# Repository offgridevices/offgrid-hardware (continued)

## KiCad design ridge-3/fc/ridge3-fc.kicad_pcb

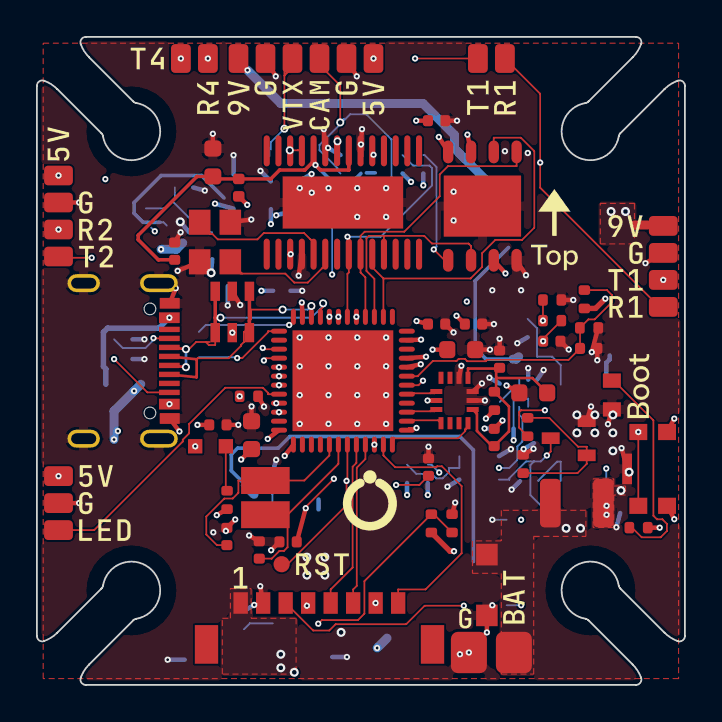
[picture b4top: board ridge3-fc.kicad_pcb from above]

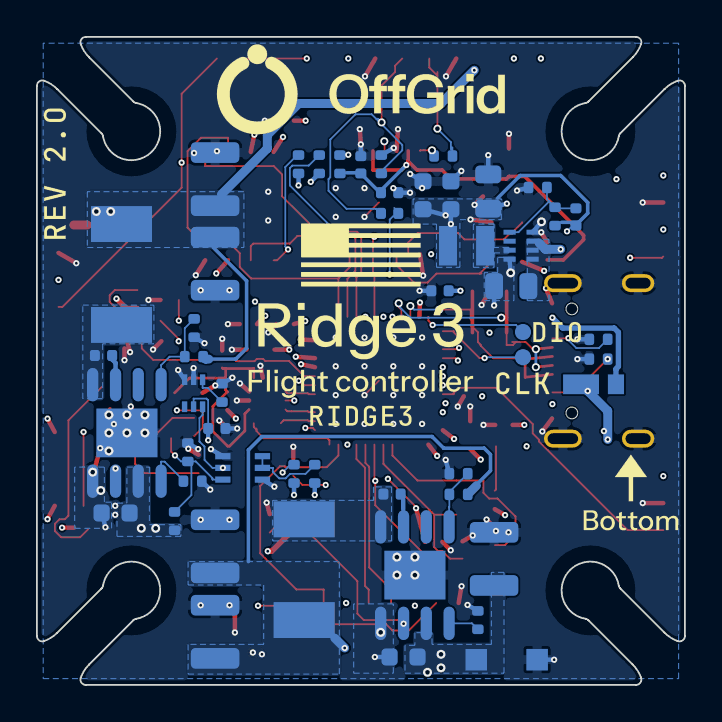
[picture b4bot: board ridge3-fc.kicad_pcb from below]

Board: 6 copper layers, 36.0 x 36.0 mm, 124 parts (51 on the bottom side), 70 nets.

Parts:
C1, C2, C5, C10, C11, C19, C20, C21, C22, C23, C26, C30, C31, C32, C34, C35, C36, C37: 100nF; C_0402_1005Metric
C3, C8: 10uF; C_1210_3225Metric
C4, C9: 100nF; C_0603_1608Metric
C6, C7, C12, C13: 22uF; C_1210_3225Metric
C14, C17: 10uF; C_0805_2012Metric
C15, C16, C25, C29, C33: 4.7uF; C_0603_1608Metric
C18, C27, C28: 10pF; C_0402_1005Metric
C24: 1uF; C_0603_1608Metric
D_TVS, D_TVS9: SMF33A; SMF_L2.8-W1.8-LS3.7-RD
D_USB: RB160VAM-40; SOD-323HE_L2.0-W1.4-LS2.5-RD
FB_OSD: 600R@100MHz; L_0402_1005Metric
H1, H2, H3, H4: HOLE; MOUNT_M2_SLOT
J_ESC: Micro-Lock Plus 8P RA; CONN-SMD_8P-P1.25_5055670871
J_USB: USB-C; USB-C-SMD_MC-311D
LED_PWR: RED; LED0603-RD_1
LED_STAT: BLUE; LED0603-R-RD_BLUE
L_3V3: 0.47uH; IND-SMD_L2.5-W2.0_TFM252012ALMA2R2MTAA
L_5V, L_9V: 15uH; IND-SMD_L7.1-W6.5_SPM6530T
P_5V: PAD_SIG
P_BAT: PAD_MOTOR
P_BATG: PAD_MOTOR
P_CAM, P_CAM5V: PAD_SIG
P_CAMG: PAD_SIG
P_G1: PAD_SIG
P_HD9V: PAD_SIG
P_HDG: PAD_SIG
P_HDR: PAD_SIG
P_HDT: PAD_SIG
P_LED: PAD_SIG
P_R1, P_R2, P_R4: PAD_SIG
P_RX5V: PAD_SIG
P_RXG: PAD_SIG
P_T1, P_T2, P_T4: PAD_SIG
P_VTX, P_VTX9V: PAD_SIG
P_VTXG: PAD_SIG
Q_TSW: BSS138DW; SC-70-6_L2.0-W1.3-P0.65-LS2.1-BL
Q_VTX: AO3400A; SOT-23-3_L2.9-W1.3-P1.90-LS2.4-BR
R1, R6, R8, R11, R14, R17, R18, R20: 100k; R_0402_1005Metric
R2, R31: 1k; R_0402_1005Metric
R3: 30k; R_0402_1005Metric
R4: 2k; R_0402_1005Metric
R5, R10: 57.6k; R_0402_1005Metric
R7, R9, R12: 24.9k; R_0402_1005Metric
R13: 100R; R_0402_1005Metric
R15: 121k; R_0402_1005Metric
R16, R24, R25, R26: 10k; R_0402_1005Metric
R19: 12.4k; R_0402_1005Metric
R21: 22.1k; R_0402_1005Metric
R22: 3.3k; R_0402_1005Metric
R23: 10R; R_0402_1005Metric
R27, R28: 75R; R_0402_1005Metric
R29, R30: 5.1k; R_0402_1005Metric
R32: 330R; R_0402_1005Metric
SW_BOOT: BOOT; SW-SMD_5P-L4.2-W2.8-P1.60-LS4.6-TR
TP_NRST: PAD_TP
TP_SWCLK: PAD_TP
TP_SWDIO: PAD_TP
U_BUCK3: TPS628501; SOT-583-8_L2.1-W1.6-P0.50-LS1.6-BL
U_BUCK5, U_BUCK9: LMR38020F; ESOP-8_L4.9-W3.9-P1.27-LS6.0-BL-EP-1
U_ESD: USBLC6-2SC6; SOT-23-6_L2.9-W1.6-P0.95-LS2.8-BL
U_FC: STM32G473CEU6; UFQFPN-48_L7.0-W7.0-P0.50-BL-EP5.6
U_FLASH: S25FL128LAGNFM010; WSON-8_L6.0-W5.0-P1.27-BL-EP
U_IMU: IIM-42652; LGA-14_L3.0-W2.5-P0.50-TL
U_OSD: AT7456E; TSSOP-28_L9.7-W4.4-P0.65-LS6.4-BL-EP-2
U_TSW: TMP390A2; SOT-563_L1.6-W1.2-P0.50-LS1.6-BR
Y1: 8MHz; OSC-SMD_2P-L3.2-W2.5
Y2: 27MHz; CRYSTAL-SMD_4P-L3.2-W2.5-BL

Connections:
+3V3: C11.1, C15.1, C16.1, C17.1, C18.1, C19.1, C20.1, C21.1, C22.1, C23.1, C24.1, C25.1, C32.1, FB_OSD.1, J_ESC.4, L_3V3.2, R16.1, R17.1, R20.1, R23.1, R24.1, R25.1, R31.1, R32.1, SW_BOOT.2, SW_BOOT.3, U_FC.1, U_FC.20, U_FC.21, U_FC.23, U_FC.35, U_FC.48, U_FLASH.3, U_FLASH.7, U_FLASH.8, U_TSW.5
+3V3_GYRO: C29.1, C30.1, C31.1, R23.2, U_IMU.5, U_IMU.8
+3V3_OSD: C33.1, C34.1, C35.1, C36.1, FB_OSD.2, R26.1, U_OSD.3, U_OSD.21, U_OSD.24
+5V: C6.1, C7.1, C14.1, D_USB.1, L_5V.2, P_5V.1, P_CAM5V.1, P_RX5V.1, R8.1, U_BUCK3.1, U_BUCK3.2, U_BUCK3.3
+9V: C12.1, C13.1, L_9V.2, P_HD9V.1, P_VTX9V.1, R18.1
ADC_CURR: C1.1, R2.2, U_FC.18
ADC_VBAT: C2.1, R3.2, R4.1, U_FC.19
BOOT0: R22.1, SW_BOOT.1, SW_BOOT.4, U_FC.46
BUCK3_FB: C18.2, R20.2, R21.1, U_BUCK3.5
BUCK3_SW: L_3V3.1, U_BUCK3.7
BUCK5_CB: C5.1, U_BUCK5.7
BUCK5_EN: R6.2, R7.1, U_BUCK5.2
BUCK5_FB: R8.2, R9.1, U_BUCK5.5
BUCK5_RT: R5.1, U_BUCK5.4
BUCK5_SW: C5.2, L_5V.1, U_BUCK5.8
BUCK9_CB: C10.1, U_BUCK9.7
BUCK9_EN: Q_TSW.6, Q_VTX.3, R11.2, R12.1, U_BUCK9.2
BUCK9_FB: R18.2, R19.1, U_BUCK9.5
BUCK9_RT: R10.1, U_BUCK9.4
BUCK9_SW: C10.2, L_9V.1, U_BUCK9.8
CAM_VIDEO: C37.1, P_CAM.1, R27.1
CUR: J_ESC.3, R1.1, R2.1
FLASH_CS: R24.2, U_FC.29, U_FLASH.1
GND: C1.2, C2.2, C3.2, C4.2, C6.2, C7.2, C8.2, C9.2, C11.2, C12.2, C13.2, C14.2, C15.2, C16.2, C17.2, C19.2, C20.2, C21.2, C22.2, C23.2, C24.2, C25.2, C26.2, C27.2, C28.2, C29.2, C30.2, C31.2, C32.2, C33.2, C34.2, C35.2, C36.2, D_TVS.2, D_TVS9.2, J_ESC.2, J_USB.1, J_USB.2, J_USB.3, J_USB.4, J_USB.A1B12, J_USB.B1A12, LED_PWR.1, P_BATG.1, P_CAMG.1, P_G1.1, P_HDG.1, P_RXG.1, P_VTXG.1, Q_TSW.1, Q_TSW.4, Q_VTX.2, R1.2, R4.2, R5.2, R7.2, R9.2, R10.2, R12.2, R14.2, R15.2, R19.2, R21.2, R22.2, R27.2, R29.2, R30.2, SW_BOOT.5, U_BUCK3.4, U_BUCK3.8, U_BUCK5.1, U_BUCK5.9, U_BUCK9.1, U_BUCK9.9, U_ESD.2, U_FC.49, U_FLASH.4, U_FLASH.9, U_IMU.6, U_IMU.7, U_IMU.9, U_OSD.4, U_OSD.20, U_OSD.23, U_OSD.29, U_TSW.2, U_TSW.3, Y2.2, Y2.4
GYRO_CS: U_FC.17, U_IMU.12
GYRO_INT: U_FC.12, U_IMU.4
HSE_IN: C27.1, U_FC.5, Y1.1
HSE_OUT: C28.1, U_FC.6, Y1.2
LED0: LED_STAT.2, U_FC.45
LED0_A: LED_STAT.1, R32.2
LED_PWR_A: LED_PWR.2, R31.2
LED_STRIP: P_LED.1, U_FC.44
M1_SIG: J_ESC.5, U_FC.8
M2_SIG: J_ESC.6, U_FC.9
M3_SIG: J_ESC.7, U_FC.10
M4_SIG: J_ESC.8, U_FC.11
NRST: C26.1, TP_NRST.1, U_FC.7
OSD_CS: R25.2, U_FC.30, U_OSD.8
OSD_RST: R26.2, U_OSD.19
OSD_VIN: C37.2, U_OSD.22
OSD_VOUT: R28.1, U_OSD.25, U_OSD.26
OSD_XI: U_OSD.5, Y2.1
OSD_XO: U_OSD.6, Y2.3
SPI1_MISO: U_FC.14, U_IMU.1
SPI1_MOSI: U_FC.15, U_IMU.14
SPI1_SCK: U_FC.13, U_IMU.13
SPI2_MISO: U_FC.27, U_FLASH.2, U_OSD.11
SPI2_MOSI: U_FC.28, U_FLASH.5, U_OSD.9
SPI2_SCK: U_FC.26, U_FLASH.6, U_OSD.10
SWCLK: TP_SWCLK.1, U_FC.37
SWDIO: TP_SWDIO.1, U_FC.36
UART1_RX: P_HDR.1, P_R1.1, U_FC.32
UART1_TX: P_HDT.1, P_T1.1, U_FC.31
UART2_RX: P_R2.1, U_FC.42
UART2_TX: P_T2.1, U_FC.41
UART4_RX: P_R4.1, U_FC.40
UART4_TX: P_T4.1, U_FC.39
USB_CC1: J_USB.A5, R29.1
USB_CC2: J_USB.B5, R30.1
USB_DM: J_USB.A7, J_USB.B7, U_ESD.3, U_ESD.4, U_FC.33
USB_DP: J_USB.A6, J_USB.B6, U_ESD.1, U_ESD.6, U_FC.34
USB_VBUS: D_USB.2, J_USB.A4B9, J_USB.B4A9, U_ESD.5
VBAT: C3.1, C4.1, D_TVS.1, J_ESC.1, R3.1, R6.1, U_BUCK5.3
VBAT_VTX: C8.1, C9.1, D_TVS9.1, P_BAT.1, R11.1, U_BUCK9.3
VTX_COOL: Q_TSW.5, R16.2, U_TSW.6
VTX_HOT_G: Q_TSW.2, Q_TSW.3, R17.2
VTX_OFF: R13.1, U_FC.43
VTX_OFF_G: Q_VTX.1, R13.2, R14.1
VTX_TSET: R15.1, U_TSW.1
VTX_VIDEO: P_VTX.1, R28.2

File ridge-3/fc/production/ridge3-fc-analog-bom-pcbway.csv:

Item #,Designator,Qty,Manufacturer Part Number,Description,Value,Package/Footprint,Type,LCSC Part #,Side
1,R19,1,0402WGF1242TCE,Resistor 12.4k 1% 0402,12.4k,R_0402_1005Metric,SMD,C11692,Bottom
2,R15,1,0402WGF1213TCE,Resistor 121k 1% 0402,121k,R_0402_1005Metric,SMD,C11693,Bottom
3,"R2,R31",2,0402WGF1001TCE,Resistor 1k 1% 0402,1k,R_0402_1005Metric,SMD,C11702,Top
4,U_FC,1,STM32G473CEU6,"MCU Cortex-M4 170 MHz 512 KB, UFQFPN-48",STM32G473CEU6,UFQFPN-48_L7.0-W7.0-P0.50-BL-EP5.6,SMD,C1342773,Top
5,Q_TSW,1,BSS138DW-7-F,"Dual N-MOSFET 50 V logic level, SOT-363, -55..150 C",BSS138DW,SC-70-6_L2.0-W1.3-P0.65-LS2.1-BL,SMD,C154900,Bottom
6,FB_OSD,1,BLM15PX601SN1D,"Ferrite bead 600 Ohm at 100 MHz, 0.9 A, 0402",600R@100MHz,L_0402_1005Metric,SMD,C160977,Top
7,"D_TVS,D_TVS9",2,SMF33A-E3-08,"TVS 33 V stand-off, 53.3 V clamp, 200 W, SMF (DO-219AB)",SMF33A,SMF_L2.8-W1.8-LS3.7-RD,SMD,C1972966,Bottom+Top
8,Y2,1,ABM8AIG-27.000MHZ-12-2Z-T3,"Crystal 27 MHz 12 pF 3225, -40..125 C, AEC-Q200",27MHz,CRYSTAL-SMD_4P-L3.2-W2.5-BL,SMD,C1985432,Top
9,Q_VTX,1,AO3400A,"N-MOSFET 30 V logic level, SOT-23",AO3400A,SOT-23-3_L2.9-W1.3-P1.90-LS2.4-BR,SMD,C20917,Top
10,"C6,C7,C12,C13",4,GRM32ER71E226KE15L,Capacitor 22uF 25V X7R 1210,22uF,C_1210_3225Metric,SMD,C21397,Bottom
11,SW_BOOT,1,KMR223GLFG,"Tact switch 4.2 x 2.8 mm SMD, gold, -40..125 C",BOOT,SW-SMD_5P-L4.2-W2.8-P1.60-LS4.6-TR,SMD,C221678,Top
12,"C14,C17",2,GRM21BZ71E106KE15L,Capacitor 10uF 25V X7R 0805,10uF,C_0805_2012Metric,SMD,C237493,Bottom
13,R13,1,0402WGF1000TCE,Resistor 100R 1% 0402,100R,R_0402_1005Metric,SMD,C25076,Top
14,R23,1,0402WGF100JTCE,Resistor 10R 1% 0402,10R,R_0402_1005Metric,SMD,C25077,Top
15,R32,1,0402WGF3300TCE,Resistor 330R 1% 0402,330R,R_0402_1005Metric,SMD,C25104,Top
16,"R27,R28",2,0402WGF750JTCE,Resistor 75R 1% 0402,75R,R_0402_1005Metric,SMD,C25133,Bottom
17,"R1,R6,R8,R11,R14,R17,R18,R20",8,0402WGF1003TCE,Resistor 100k 1% 0402,100k,R_0402_1005Metric,SMD,C25741,Bottom+Top
18,"R16,R24,R25,R26",4,0402WGF1002TCE,Resistor 10k 1% 0402,10k,R_0402_1005Metric,SMD,C25744,Bottom
19,R3,1,0402WGF3002TCE,Resistor 30k 1% 0402,30k,R_0402_1005Metric,SMD,C25776,Top
20,"R7,R9,R12",3,0402WGF2492TCE,Resistor 24.9k 1% 0402,24.9k,R_0402_1005Metric,SMD,C25874,Bottom+Top
21,R22,1,0402WGF3301TCE,Resistor 3.3k 1% 0402,3.3k,R_0402_1005Metric,SMD,C25890,Top
22,"R29,R30",2,0402WGF5101TCE,Resistor 5.1k 1% 0402,5.1k,R_0402_1005Metric,SMD,C25905,Bottom
23,"R5,R10",2,0402WGF5762TCE,Resistor 57.6k 1% 0402,57.6k,R_0402_1005Metric,SMD,C26983,Bottom
24,LED_STAT,1,SMLD12BN1WT86,"LED blue 0603, -40..100 C",BLUE,LED0603-R-RD_BLUE,SMD,C2837822,Top
25,LED_PWR,1,SML-D15UWT86,"LED red 0603, -40..100 C",RED,LED0603-RD_1,SMD,C2962748,Top
26,U_IMU,1,IIM-42652,"6-axis IMU (TDK InvenSense, industrial, -40..105 C), SPI, LGA-14 2.5x3",IIM-42652,LGA-14_L3.0-W2.5-P0.50-TL,SMD,C2988404,Top
27,"C1,C2,C5,C10,C11,C19,C20,C21,C22,C23,C26,C30,C31,C32,C34,C35,C36,C37",18,CL05B104KB54PNC,Capacitor 100nF 50V X7R 0402,100nF,C_0402_1005Metric,SMD,C307331,Bottom+Top
28,"L_5V,L_9V",2,SPM6530T-150M-HZ,"Inductor 15 uH, Isat 3.0 A, 7.1 x 6.5 x 3.0 mm, AEC-Q200, 125 C",15uH,IND-SMD_L7.1-W6.5_SPM6530T,SMD,C307809,Bottom
29,U_BUCK3,1,TPS628501DRLR,"Buck 2.7-6 V in, 1 A, 150 C, SOT-583",TPS628501,SOT-583-8_L2.1-W1.6-P0.50-LS1.6-BL,SMD,C3193207,Bottom
30,"C3,C8",2,UMK325AB7106KM-T,Capacitor 10uF 50V X7R 1210,10uF,C_1210_3225Metric,SMD,C386167,Bottom+Top
31,L_3V3,1,TFM252012ALMAR47MTAA,"Inductor 0.47 uH 4.9 A, 2.5 x 2.0 mm, -55..150 C",0.47uH,IND-SMD_L2.5-W2.0_TFM252012ALMA2R2MTAA,SMD,C404800,Bottom
32,R4,1,0402WGF2001TCE,Resistor 2k 1% 0402,2k,R_0402_1005Metric,SMD,C4109,Top
33,R21,1,0402WGF2212TCE,Resistor 22.1k 1% 0402,22.1k,R_0402_1005Metric,SMD,C43473,Bottom
34,"U_BUCK5,U_BUCK9",2,LMR38020FDDAR,"Buck 80 V in, 2 A, FPWM, SO-8 PowerPAD",LMR38020F,ESOP-8_L4.9-W3.9-P1.27-LS6.0-BL-EP-1,SMD,C5149193,Bottom
35,J_USB,1,USB4105-GF-A-120,"USB-C receptacle USB 2.0, 16 contacts",USB-C,USB-C-SMD_MC-311D,SMD,C5184243,Top
36,U_TSW,1,TMP390A2DRLR,"Temperature switch, resistor-set trip, open drain, SOT-563",TMP390A2,SOT-563_L1.6-W1.2-P0.50-LS1.6-BR,SMD,C5219772,Bottom
37,J_ESC,1,5055670871,"Molex Micro-Lock Plus 1.25 mm 8-pin right-angle SMD, locking",Micro-Lock Plus 8P RA,CONN-SMD_8P-P1.25_5055670871,SMD,C585387,Top
38,U_FLASH,1,S25FL128LAGNFM010,"128 Mbit SPI NOR flash, -40..125 C (AEC-Q100 grade 1), WSON-8 5x6",S25FL128LAGNFM010,WSON-8_L6.0-W5.0-P1.27-BL-EP,SMD,C5880817,Top
39,D_USB,1,RB160VAM-40TR,"Schottky 40 V 1 A, SOD-323HE",RB160VAM-40,SOD-323HE_L2.0-W1.4-LS2.5-RD,SMD,C703624,Bottom
40,U_ESD,1,USBLC6-2SC6,"USB ESD protection, SOT-23-6",USBLC6-2SC6,SOT-23-6_L2.9-W1.6-P0.95-LS2.8-BL,SMD,C7519,Top
41,"C18,C27,C28",3,GRM1555C1H100JA01D,Capacitor 10pF 50V C0G 0402,10pF,C_0402_1005Metric,SMD,C76946,Bottom+Top
42,"C4,C9",2,GRM188R72A104KA35D,Capacitor 100nF 100V X7R 0603,100nF,C_0603_1608Metric,SMD,C77058,Bottom
43,U_OSD,1,AT7456E,"Analog video OSD (MAX7456-compatible), HTSSOP-28-EP",AT7456E,TSSOP-28_L9.7-W4.4-P0.65-LS6.4-BL-EP-2,SMD,C82351,Top
44,C24,1,GCM188R71E105KA64D,Capacitor 1uF 25V X7R 0603,1uF,C_0603_1608Metric,SMD,C85862,Top
45,Y1,1,NX3225GD-8MHZ-STD-CRA-3,"Crystal 8 MHz 8 pF 3225, -40..150 C, AEC-Q200",8MHz,OSC-SMD_2P-L3.2-W2.5,SMD,C889706,Top
46,"C15,C16,C25,C29,C33",5,GRM188Z71A475KE15D,Capacitor 4.7uF 10V X7R 0603,4.7uF,C_0603_1608Metric,SMD,C913474,Bottom+Top

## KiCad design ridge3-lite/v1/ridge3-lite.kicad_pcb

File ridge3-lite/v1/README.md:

# Ridge 3 Lite — v1

**One board that does it all:** the flight controller and the 4-in-1 ESC of a
3-inch quad on a single 38 × 38 mm board, for Project Cheap Drone Phase 1. A
battery lead and four motors connect to it, and it flies on stock Betaflight.
It has no FPV parts: no OSD, no video transmitter, no camera connector.

It replaces the GEPRC TAKER G4 AIO that Phase 1 flew. It uses the same
25.5 mm mounting pattern, and Betaflight's own TAKERG4AIO target runs on it
pin for pin.

> **Status: design complete, not yet built.** The board is fully routed
> (`ridge3-lite.kicad_pcb`): KiCad 10 DRC 0 errors, 0 warnings, 0
> unconnected, every fab gate and all 100 checks in `VERIFICATION.md` pass,
> and Gerbers, BOM, CPL and renders are in `production/` and `images/`.
> Nothing has been measured on hardware: build a few and go through
> bring-up before a volume order.

## This revision

| | |
|---|---|
| Revision | **v1** (product: [`../README.md`](../README.md)) |
| Status | designed, not yet built |
| Tests and simulations | [`TESTS.md`](TESTS.md): every one with its v1 result |
| Trade-offs | [`docs/decisions.md`](docs/decisions.md) |
| Toolchain | KiCad 10.0.6 (pinned image, `tools/Dockerfile`) |
| Brand | OffGrid v3.2.2 ([`docs/brand.md`](../../docs/brand.md)) |

## Requirements

What the board was designed to meet, as the owner set them, and where v1
stands.

| Requirement | v1 |
|---|---|
| One board: flight controller + 4-in-1 ESC for the Phase 1 3" quad | ✅ 38 × 38 mm, 25.5 mm mount |
| No FPV parts | ✅ none |
| **Parts in production and readily available, for a 10,000-board run** | ✅ every part active, second sources and lead times listed (`docs/lifecycle.md`, `docs/sourcing-10k.md`, checked Oct 2026: re-check before ordering) |
| Orderable from JLCPCB or PCBWay | ✅ files for both in `production/` |
| Never burns out under full stress in desert heat | ✅ in simulation: the ESC's 100 °C limit throttles before damage (`TESTS.md`); ⏳ to confirm on hardware |
| Per-motor current limiting | ✅ a shunt and amplifier per motor, AM32's limit |
| Flashing firmware is all it takes | ✅ stock Betaflight target; the four ESCs need AM32 flashed once over SWD |
| Stable flight | ✅ gyro orientation checked against Betaflight's maths; ⏳ to fly |
| Cheap | ⏳ priced at the first order (8 layers and fine rules cost more: `docs/decisions.md`) |
| Beautiful: OffGrid logo, American flag, clean layout | ✅ logo and flag; the flag is silkscreen only (no room for the gold one) |
| KiCad 10 only | ✅ KiCad 10.0.6 |
| 35 mm if possible, 38 mm accepted | 38 mm (35 could not be routed) |

## Next steps

1. **Order 5–10 prototypes** (see *Ordering*). Re-read stock first
   (`tools/lcsc.py`): the part audits in `docs/` are dated.
2. **Bring them up** (see *Bring-up*): flash Betaflight and AM32, motor
   order and direction, gyro direction.
3. **Measure against the simulations:** board and FET temperatures at
   hover and on punches, current-sense readings against a meter, gyro noise.
   Record the results here and correct the models if they disagree.
4. **Design the frame** from `mechanical/` (25.5 mm M2 soft mounts), with a
   canopy or top plate to keep sun off the board.
5. **Then a volume order.** Changes that need new copper go into `v2/`
   (`docs/decisions.md` lists the ideas).

Why the board is the way it is: [`docs/decisions.md`](docs/decisions.md).

| | |
|---|---|
| Size | 38 × 38 mm, 3 mm corner radius, 25.5 mm M2 holes for soft-mount grommets |
| Battery | 2–4S LiPo, 4S HV (17.4 V) included; XT30 lead on solder pads |
| Motors | 4 × brushless, up to 15 A each continuous, 25 A peak (per-motor current limit) |
| Flight controller | STM32G473CEU6, ICM-42688-P gyro (BMI270 as second source), Betaflight |
| ESCs | 4 × STM32G071 + TI DRV8300D + 6 × Toshiba TPN2R304PL (40 V, 2.3 mΩ), AM32 |
| Power | 5 V 0.6 A BEC (TI LMR36506, 70 V input), 3.3 V for the FC and the ESCs, 11 V gate drive |
| Sensing | battery voltage and current to Betaflight; per-motor current and voltage to each ESC |
| PCB | 8 layers, 1.6 mm, 1 oz copper on every layer, 0.09 mm track and gap, vias down to 0.37 / 0.15 mm, every via filled and capped |

---

## What's on the board

- **Flight controller (top centre).** The STM32G473 runs Betaflight. It has:
  - the gyro on SPI1;
  - an 8 MHz crystal;
  - USB-C with ESD protection;
  - a BOOT button;
  - status and power LEDs;
  - a buzzer switch.

  There is no blackbox flash; log to an OpenLager on UART1 if needed.
- **Four ESCs, one per edge (bottom).** Each motor channel is the same layout,
  turned 90° per edge. Each has:
  - its own STM32G071 running AM32 (stock GEN_64K_G071 target);
  - a DRV8300D gate driver with 22 Ω / 10 Ω gate resistors, chosen by
    simulation to keep the FETs inside 40 V;
  - six FETs;
  - a 0.5 mΩ Kelvin shunt with an INA186 amplifier, so the ESC limits each
    motor's current itself;
  - back-EMF sensing and battery-voltage sensing.
- **Power.**
  - A 70 V-rated buck makes 5 V for the receiver and the LDOs.
  - A 60 V-rated LDO makes the 11 V gate drive.
  - A 22 V TVS clamps spikes on the battery.
  - The board runs from USB alone for configuration: everything powers up
    except the motors.
- **Pads.**
  - Battery + and − at the rear edge.
  - Three motor pads at each edge.
  - The receiver (UART2, 5 V, G) at the front.
  - Aux (UART1, LED strip, buzzer) at the right.
  - USB-C at the left.
  - SWD test points for each ESC's first flash, plated through so a probe
    reaches them from either side.

## Ordering

JLCPCB or PCBWay, from `production/`:

- **8 layers, 1.6 mm, 1 oz copper on every layer.** Layers: F (parts, power) / In1
  ground plane / In2-In4 signals (In3 and In4's leftover copper is battery) / In5 the
  channels' return pours / In6 battery plane / B (parts, power).
- **0.09 mm (3.5 mil) track and gap, vias down to 0.37 / 0.15 mm** (also 0.4 / 0.2 and 0.5 / 0.25 mm). Both are inside
  JLCPCB's multilayer capability, but they are its fine-line and small-via
  price tiers: expect them on the quote. The board needs them: 260 parts on
  38 mm leave no room for 0.1 mm rules. Going to 40 mm would not help (the
  congestion is round the flight controller in the middle, not at the edges).
- **Matte black solder mask, white silkscreen, ENIG.**
- **Via-in-pad: "Epoxy filled & capped" (POFV).** Every via is filled; on 6+
  layers JLCPCB does this at no extra charge.
- Assembly: upload the BOM and CPL from `production/`. All assembled parts
  are on both sides; JLCPCB's two-sided assembly.
- **Fit by hand after assembly:**
  - the XT30 battery lead on the battery pads;
  - the bulk capacitor across the same pads (`docs/bulk-capacitor.md`:
    2 × Rubycon 35PZK470M10X11, or 1 × Panasonic EEH-AZSV681UB);
  - the motor wires.

**Check before you pay:** the SMF22A-TP's cathode band must face pad 1 (battery
+) in JLCPCB's placement preview. MCC's library symbol does not mark it.

## Bring-up

Firmware and every setting are in `firmware/`, with a README that walks
through it. In short:

1. USB only: flash Betaflight. Use the stock TAKERG4AIO target, or this
   board's RIDGE3LITE build; both are in `firmware/betaflight/`. Then paste
   `cli-setup.txt`.
2. Still on USB: flash each ESC's AM32 bootloader and firmware once over SWD
   (`firmware/am32/flash_esc.sh`). Then set them in ESC-configurator through
   Betaflight passthrough (`esc-settings.md`).
3. Battery, props off:
   - check motor order and direction in Betaflight's Motors tab;
   - check that the gyro moves the right way. The IMU sits at 135°; see
     `firmware/gyro-orientation.md`.

## What was checked

The full record, with dates: [`TESTS.md`](TESTS.md). In short:

The first five rows are gates: `src/make.py` stops if one fails, and CI
(`ci / ridge3-lite-v1`) runs them on every push, after rebuilding the
artwork from `src/` on the committed routed board.

| Check | Result |
|---|---|
| Every part has a footprint and an LCSC number; every pin is on its footprint; no single-pin net | pass, 260 parts |
| Routed board, KiCad 10 DRC | 0 errors, 0 warnings, 0 unconnected |
| Every pad's net on the board equals `src/circuit.py`; BOM and CPL list exactly the 223 placed parts | pass |
| Committed Gerbers, drills, BOM, CPL and netlist equal what `make.py` builds (`tools/check_outputs.py`) | pass |
| Design checks (`src/verify.py` → `VERIFICATION.md`): firmware pin maps against Betaflight TAKERG4AIO and AM32 GEN_64K_G071, gyro orientation, parts, fab outputs, simulation verdicts | 100 passed, 0 failed |
| Every part in production (`docs/lifecycle.md`, dated audit) | 45 parts checked; 2 swapped for active parts |
| Volume sourcing for 10,000 boards (`docs/sourcing-10k.md`, dated audit) | second sources and factory lead times listed |

### Simulation (`sim/`)

Worst case: a 4S HV pack (17.4 V), XING2 1404 3800KV on 3" props
(15 A per motor sustained, 25 A stalled).

- **Half-bridge switching (ngspice, fitted FET model).**
  - Peak FET voltage is 29.7–32.2 V at 15 A and 39.4 V at 30 A with 4 nH of
    loop, against the FETs' 40 V. The 22 / 10 Ω gate resistors fixed a
    41–50 V overshoot found in the first draft.
  - The switch node slews at most 1.85 V/ns.
- **Battery spikes.**
  - 18.6 V worst with the bulk capacitor fitted; the TVS never conducts in
    normal use.
  - Unplugging the pack while the motors brake reaches 57 V. No TVS this
    size can absorb that: keep the lead soldered or the XT30 seated.
- **Gate supply, BEC, sense chains.** All within ratings at a 100 °C board.
  The current sense reads 20 mV/A per ESC and 12 mV/A total.
- **Thermal (finite-volume model of the routed eight-layer board; `sim/thermal/`).**
  Validated against Toshiba's published Rth(ch-a) to within 2 %.

### Heat: what the board can do on a hot day

The routed board as ordered (8 layers, 1 oz, bare, no heat sink), 50 °C air,
1000 W/m² of sun on the board, prop wash (`sim/thermal/`, `--case desert`):

| Flight | FET (limit 175) | ESC MCU (105) | Gyro (85) |
|---|---|---|---|
| Armed on the ground, still air | 74 °C | 79 °C | |
| Hover | 98 °C | 95 °C | **89 °C** |
| Cruise | 110 °C | 101 °C | |
| 8 punches of 3 s full throttle | 119 °C | 110 °C | |
| Full throttle, 60 s | 165 °C | **154 °C** | **120 °C** |
| Motor 1 stalled at 25 A for 2 s | **179 °C** | 102 °C | |

At 25 °C in the shade, hover is 67 / 64 / 57 °C and 60 s of full throttle is
130 / 119 / 88 °C.  With half the prop wash, 60 s of full throttle would reach
225 °C: on such a day the ESCs' temperature limit, not the copper, is what
keeps the board alive.  Channel 1 runs hottest: it sits by the battery pads,
where all 60 A enter.  Its FETs are 40 °C above channel 4's at full throttle.

**What this means.**
- In normal flying on a normal day nothing comes near a limit.
- On a 50 °C day in direct sun the board will not burn out. Each ESC's
  temperature limit (AM32, 100 °C on its own chip) throttles that motor back
  first. The ESC chip tracks its FETs closely (154 against 165 °C at the end
  of the 60 s run), so the cut-back starts with the FETs near 110 °C, far
  under their 175 °C. Sustained full throttle on such a day is therefore
  throttled (by about two thirds on the placed board's estimate,
  `sim/thermal/results-size-cooling.md`), more if the prop wash is weak.
- A jammed prop is cut by AM32's stuck-rotor protection; the 2 s stall above
  is the case where it fails to act, and stays within 4 °C of the FET rating.
- Short punches are fine.
- Under those conditions the gyro runs slightly over its rated 85 °C even at
  hover, and Betaflight's gyro drifts with temperature.

**Fixes, in order of value:**
1. Keep the sun off the board. A frame top plate or a canopy over the stack
   removes the 1000 W/m² of sun, the largest single input at hover.
2. A finned aluminium top sink (9.6 g, 4 mm fins) takes 25–35 °C off at full
   throttle.

The full tables, with every cooling option, 35 against 38 mm and 1 against
2 oz, are in `sim/thermal/results-size-cooling.md`.

## Limits

- **Battery:** 2–4S. 5S and up exceed the FETs' 40 V rating under switching
  spikes.
- **The pack must stay connected while the motors spin** (see the 57 V
  case above).
- **Motors:** keep each ESC's current limit at 26 A or lower (`esc-settings.md`).
- **Bulk capacitor:** it must be fitted. Without it the battery ripple is
  2–7 V p-p and a hot plug rings to 26 V.

## Build

Everything runs in the pinned toolchain image (`tools/Dockerfile`: KiCad
10.0.6 by digest, Freerouting, ngspice). Build it once as the Dockerfile's
header says, then from this folder:

```
tools/kd python3 src/make.py            # gates and every output from the committed board
tools/kd python3 src/make.py --artwork  # lay the silkscreen out again first
tools/kd python3 src/verify.py          # design checks, writes VERIFICATION.md
tools/kd sh sim/run_all.sh              # circuit simulations
tools/kd python3 sim/thermal/thermal.py ridge3-lite.kicad_pcb --case desert
```

### Changing this board

Edit the source, rebuild, commit the outputs with it. CI (`ci /
ridge3-lite-v1`) rebuilds and fails if the committed files do not match.

| To change | Edit | Then run |
|---|---|---|
| A part number (same footprint) | `src/parts.py` | `make.py` (BOM and CPL) |
| Silkscreen labels, logo, flag | `src/silk.py`, `src/brand.py` | `make.py --artwork` |
| Design rules | `src/pcb.py` (`RULES`) | `make.py` (rewrites `.kicad_dru`, re-runs DRC) |
| Betaflight / AM32 settings | `firmware/` | `verify.py` |
| Simulation inputs | `sim/` | `sim/run_all.sh`, `thermal.py` |
| Connections, placement or copper | `src/circuit.py`, `src/layout.py`, ... | a new revision: copy to `v2/`, `make.py --reroute`, finish and check it |

The net gate stops the build if `src/circuit.py` and the routed board
disagree, so a circuit change cannot slip into v1's fab files.

The committed `ridge3-lite.kicad_pcb` is the design of record. `make.py
--reroute` places and routes from scratch, but the last connection (C2 to
the BEC input) and one ground via were placed by hand, so a reroute is a
starting point for a new revision, not a rebuild of this one.

## Files

```
README.md                  this file
TESTS.md                   every test and simulation with its v1 result
VERIFICATION.md            every design check and its result (written by src/verify.py)
ridge3-lite.kicad_pcb      the routed board (design of record), with .kicad_pro / .kicad_dru
production/                Gerber zip, BOM and CPL (JLCPCB, PCBWay), netlist, assembly PDF
images/                    renders and the silkscreen read back from the Gerbers
mechanical/                STEP model of the assembled board (zipped)
firmware/                  Betaflight and AM32 hex files, settings, flashing scripts
docs/                      decisions and trade-offs, part audits (dated), bulk capacitor, gyro second source
sim/                       circuit simulations (ngspice) and the thermal model
src/                       the generator: circuit, footprints, placement, power copper, routing, artwork, checks
og.pretty/, og.3dshapes/   this board's footprints and their 3D models
fonts/                     brand fonts for the silkscreen (OFL)
tools/                     the pinned toolchain (Docker), CI output check, sourcing scrapers
```

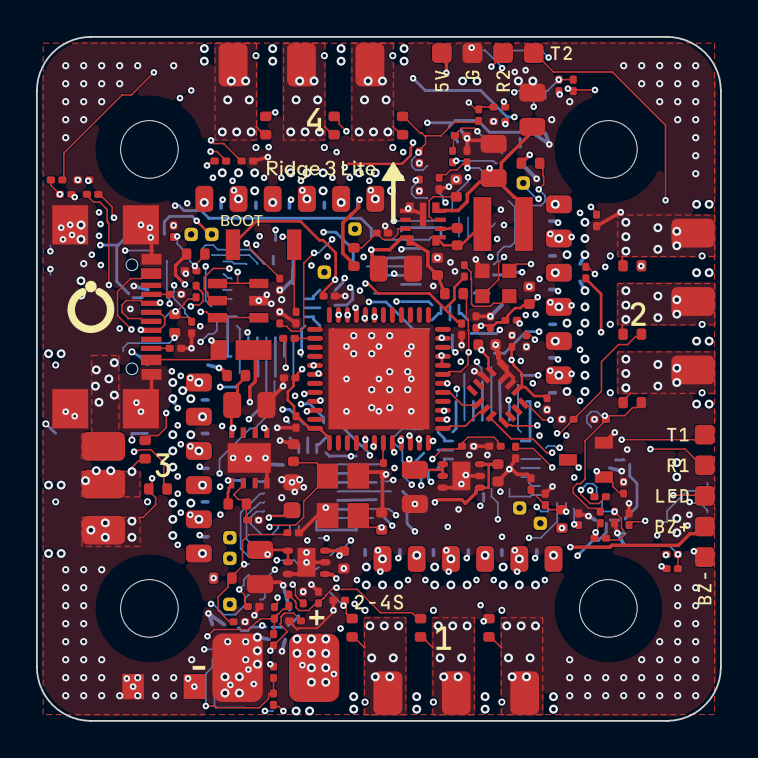
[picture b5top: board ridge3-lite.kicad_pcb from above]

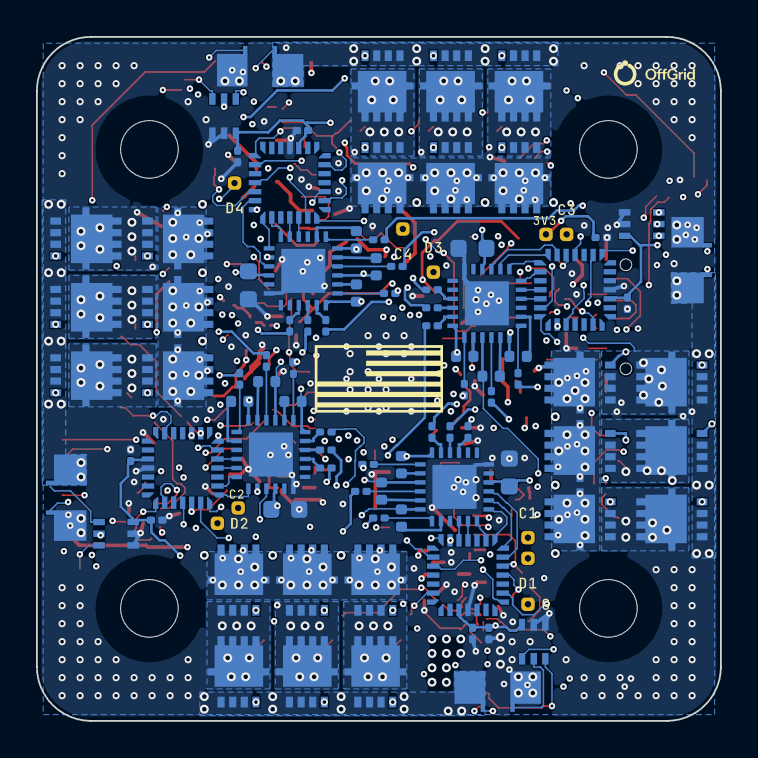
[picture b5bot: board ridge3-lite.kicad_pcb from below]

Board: 8 copper layers, 38.0 x 38.0 mm, 260 parts (88 on the bottom side), 188 nets.

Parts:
C1, C8, C10, C11, C104, C106, C108, C204, C206, C208, C304, C306, C308, C404, C406, C408: 4.7uF; C_0805_2012Metric
C2, C3: 100nF; C_0402_1005Metric_L
C4, C7, C9, C103, C105, C107, C203, C205, C207, C303, C305, C307, C403, C405, C407: 1uF; C_0402_1005Metric_L
C5, C6: 22uF; C_0805_2012Metric
C12, C102, C202, C302, C402: 10uF; C_0603_1608Metric_L
C13, C14, C15, C16, C17, C18, C19, C22, C26, C27, C101, C109, C110, C111, C201, C209, C210, C211, C301, C309, C310, C311, C401, C409, C410, C411: 100nF; C_0201_0603Metric_L
C20: 1uF; C_0201_0603Metric_L
C21, C25: 4.7uF; C_0402_1005Metric_L
C23, C24: 12pF; C_0402_1005Metric_L
D_TVS: SMF22A; SOD-123FL_L2.8-W1.9-LS3.7-RD
D_USB: SS1040HE; SOD-323HE_L2.0-W1.4-LS2.5-RD
H1, H2, H3, H4: HOLE; MOUNT_M2
J_USB: USB-C; USB-C-SMD_TYPE-C-16P-USB4110-GF-A
LED_PWR: red; LED0603-RD
LED_STAT: blue; LED0603-RD
L_BEC: 10uH; IND-SMD_L3.0-W3.0_SWPA3010S
P_5V: PAD_SIG
P_BAT+: PAD_BAT
P_BAT-: PAD_BAT
P_BZ+: PAD_SIG
P_BZ-: PAD_SIG
P_G: PAD_SIG
P_LED: PAD_SIG
P_M1A, P_M1B, P_M1C, P_M2A, P_M2B, P_M2C, P_M3A, P_M3B, P_M3C, P_M4A, P_M4B, P_M4C: PAD_MOTOR
P_R1, P_R2: PAD_SIG
P_T1, P_T2: PAD_SIG
Q1AH, Q1AL, Q1BH, Q1BL, Q1CH, Q1CL, Q2AH, Q2AL, Q2BH, Q2BL, Q2CH, Q2CL, Q3AH, Q3AL, Q3BH, Q3BL, Q3CH, Q3CL, Q4AH, Q4AL, Q4BH, Q4BL, Q4CH, Q4CL: TPN2R304PL; TSON-8_L3.1-W3.1-P0.65-LS3.3-BL-EP
Q_BZ: AO3400A; SOT-23-3_L2.9-W1.3-P1.90-LS2.4-BR
R1, R119, R219, R319, R419: 100k; R_0402_1005Metric_L
R2: 27k; R_0201_0603Metric_L
R3: 10R; R_0402_1005Metric_L
R4: 82k; R_0402_1005Metric_L
R5, R9, R16, R105, R110, R115, R118, R120, R205, R210, R215, R218, R220, R305, R310, R315, R318, R320, R405, R410, R415, R418, R420: 10k; R_0201_0603Metric_L
R6, R103, R108, R113, R203, R208, R213, R303, R308, R313, R403, R408, R413: 10k; R_0402_1005Metric_L
R7, R13, R117, R217, R317, R417: 1k; R_0201_0603Metric_L
R8: 62k; R_0201_0603Metric_L
R10, R102, R107, R112, R202, R207, R212, R302, R307, R312, R402, R407, R412: 10R; R_0201_0603Metric_L
R11, R12: 5.1k; R_0201_0603Metric_L
R14: 330R; R_0201_0603Metric_L
R15: 100R; R_0201_0603Metric_L
R101, R106, R111, R201, R206, R211, R301, R306, R311, R401, R406, R411: 22R; R_0201_0603Metric_L
R104, R109, R114, R204, R209, R214, R304, R309, R314, R404, R409, R414: 2.2k; R_0201_0603Metric_L
R116, R216, R316, R416: 1.5k; R_0201_0603Metric_L
R_S1, R_S2, R_S3, R_S4: 0.5mOhm; RES-SMD_1206_HCS1206
SW_BOOT: BOOT; KEY-SMD_B3U-1000PM
TP_3V3: PAD_TP
TP_C1, TP_C2, TP_C3, TP_C4: PAD_TP
TP_D1, TP_D2, TP_D3, TP_D4: PAD_TP
TP_GND: PAD_TP
U_A1, U_A2, U_A3, U_A4: INA186A3; SC-70-6_L2.0-W1.3-P0.65-LS2.1-BL-1
U_BEC: LMR36506R5; VQFN-9_L2.1-W2.1-P0.50-TL
U_D1, U_D2, U_D3, U_D4: DRV8300DRGER; VQFN-24_L4.0-W4.0-P0.50-TL-EP2.5
U_E1, U_E2, U_E3, U_E4: STM32G071GBU6; UFQFPN-28_L4.0-W4.0-P0.50-BL
U_ESD: USBLC6-2SC6; SOT-23-6_L2.9-W1.6-P0.95-LS2.8-BL
U_FC: STM32G473CEU6; UFQFPN-48_L7.0-W7.0-P0.50-BL-EP5.6
U_GVDD: TPS7A1601; SON-8_L3.0-W3.0-P0.65-TL-EP
U_IMU: ICM-42688-P; LGA-14_L3.0-W2.5-P0.50-TL
U_LDO: TLV76733; WSON-6_L2.0-W2.0-P0.65-TL-EP
U_LDOE: TLV76733; WSON-6_L2.0-W2.0-P0.65-TL-EP
Y1: 8 MHz; CRYSTAL-SMD_4P-L3.2-W2.5-BL

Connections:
+3V3: C8.1, C15.1, C16.1, C17.1, C18.1, C19.1, C20.1, C21.1, R10.1, R13.1, R14.1, SW_BOOT.1, U_FC.1, U_FC.20, U_FC.21, U_FC.23, U_FC.35, U_FC.48, U_LDO.1, U_LDO.2
+3V3E: C10.1, C101.1, C109.1, C201.1, C209.1, C301.1, C309.1, C401.1, C409.1, TP_3V3.1, U_A1.3, U_A2.3, U_A3.3, U_A4.3, U_E1.3, U_E2.3, U_E3.3, U_E4.3, U_LDOE.1, U_LDOE.2
+3V3_GYRO: C25.1, C26.1, C27.1, R10.2, U_IMU.5, U_IMU.8
+5V: C5.1, C6.1, C7.1, C9.1, D_USB.1, L_BEC.2, P_5V.1, P_BZ+.1, U_BEC.8, U_LDO.4, U_LDO.6, U_LDOE.4, U_LDOE.6
ADC_VBAT: C13.1, R6.2, R7.1, U_FC.19
BEC_BOOT: C3.1, U_BEC.6
BEC_EN: R1.2, R2.1, U_BEC.3
BEC_SW: C3.2, L_BEC.1, U_BEC.5
BEC_VCC: C4.1, U_BEC.7
BEEPER: R15.1, U_FC.38
BEEPER_G: Q_BZ.1, R15.2, R16.1
BOOT0: R9.1, SW_BOOT.2, U_FC.46
BZ-: P_BZ-.1, Q_BZ.3
CUR: C14.1, R8.1, R118.2, R218.2, R318.2, R418.2, U_FC.18
GND: C1.2, C2.2, C4.2, C5.2, C6.2, C7.2, C8.2, C9.2, C10.2, C11.2, C12.2, C13.2, C14.2, C15.2, C16.2, C17.2, C18.2, C19.2, C20.2, C21.2, C22.2, C23.2, C24.2, C25.2, C26.2, C27.2, C101.2, C102.2, C109.2, C110.2, C111.2, C201.2, C202.2, C209.2, C210.2, C211.2, C301.2, C302.2, C309.2, C310.2, C311.2, C401.2, C402.2, C409.2, C410.2, C411.2, D_TVS.2, J_USB.8, J_USB.9, J_USB.10, J_USB.11, J_USB.A1B12, J_USB.B1A12, LED_PWR.1, P_BAT-.1, P_G.1, Q_BZ.2, R2.2, R5.2, R7.2, R8.2, R9.2, R11.2, R12.2, R16.2, R104.2, R109.2, R114.2, R117.2, R120.2, R204.2, R209.2, R214.2, R217.2, R220.2, R304.2, R309.2, R314.2, R317.2, R320.2, R404.2, R409.2, R414.2, R417.2, R420.2, R_S1.2, R_S2.2, R_S3.2, R_S4.2, TP_GND.1, U_A1.1, U_A1.2, U_A2.1, U_A2.2, U_A3.1, U_A3.2, U_A4.1, U_A4.2, U_BEC.1, U_BEC.9, U_D1.6, U_D1.25, U_D2.6, U_D2.25, U_D3.6, U_D3.25, U_D4.6, U_D4.25, U_E1.4, U_E2.4, U_E3.4, U_E4.4, U_ESD.2, U_FC.49, U_GVDD.4, U_GVDD.9, U_IMU.6, U_IMU.7, U_IMU.9, U_LDO.3, U_LDO.5, U_LDO.7, U_LDOE.3, U_LDOE.5, U_LDOE.7, Y1.2, Y1.4
GVDD: C12.1, C102.1, C202.1, C302.1, C402.1, R4.1, U_D1.4, U_D2.4, U_D3.4, U_D4.4, U_GVDD.1
GVDD_FB: R4.2, R5.1, U_GVDD.2
GVDD_IN: C11.1, R3.2, U_GVDD.5, U_GVDD.8
GYRO_CS: U_FC.17, U_IMU.12
GYRO_INT: U_FC.12, U_IMU.4
HSE_IN: C23.1, U_FC.5, Y1.1
HSE_OUT: C24.1, U_FC.6, Y1.3
LED0: LED_STAT.1, U_FC.45
LED0_A: LED_STAT.2, R14.2
LED_PWR_A: LED_PWR.2, R13.2
LED_STRIP: P_LED.1, U_FC.44
M1_A: C103.2, P_M1A.1, Q1AH.1, Q1AH.2, Q1AH.3, Q1AL.5, Q1AL.6, Q1AL.7, Q1AL.8, Q1AL.9, R103.1, U_D1.18
M1_B: C105.2, P_M1B.1, Q1BH.1, Q1BH.2, Q1BH.3, Q1BL.5, Q1BL.6, Q1BL.7, Q1BL.8, Q1BL.9, R108.1, U_D1.15
M1_BSTA: C103.1, U_D1.20
M1_BSTB: C105.1, U_D1.17
M1_BSTC: C107.1, U_D1.14
M1_C: C107.2, P_M1C.1, Q1CH.1, Q1CH.2, Q1CH.3, Q1CL.5, Q1CL.6, Q1CL.7, Q1CL.8, Q1CL.9, R113.1, U_D1.12
M1_CMP_A: R103.2, R104.1, R105.1, U_E1.27
M1_CMP_B: R108.2, R109.1, R110.1, U_E1.23
M1_CMP_C: R113.2, R114.1, R115.1, U_E1.8
M1_GHA: Q1AH.4, R101.2
M1_GHA_D: R101.1, U_D1.19
M1_GHB: Q1BH.4, R106.2
M1_GHB_D: R106.1, U_D1.16
M1_GHC: Q1CH.4, R111.2
M1_GHC_D: R111.1, U_D1.13
M1_GLA: Q1AL.4, R102.2
M1_GLA_D: R102.1, U_D1.11
M1_GLB: Q1BL.4, R107.2
M1_GLB_D: R107.1, U_D1.10
M1_GLC: Q1CL.4, R112.2
M1_GLC_D: R112.1, U_D1.9
M1_HA: U_D1.22, U_E1.19
M1_HB: U_D1.23, U_E1.18
M1_HC: U_D1.24, U_E1.16
M1_IOUT: R116.1, R118.1, U_A1.6
M1_ISENSE: C110.1, R116.2, R117.1, U_E1.11
M1_LA: U_D1.1, U_E1.15
M1_LB: U_D1.2, U_E1.14
M1_LC: U_D1.3, U_E1.13
M1_NEUTRAL: R105.2, R110.2, R115.2, U_E1.9
M1_SIG: U_E1.24, U_FC.8
M1_SNSN: R_S1.4, U_A1.5
M1_SNSP: R_S1.3, U_A1.4
M1_SRC: C104.2, C106.2, C108.2, Q1AL.1, Q1AL.2, Q1AL.3, Q1BL.1, Q1BL.2, Q1BL.3, Q1CL.1, Q1CL.2, Q1CL.3, R_S1.1
M1_SWCLK: TP_C1.1, U_E1.21
M1_SWDIO: TP_D1.1, U_E1.20
M1_VSENSE: C111.1, R119.2, R120.1, U_E1.12
M2_A: C203.2, P_M2A.1, Q2AH.1, Q2AH.2, Q2AH.3, Q2AL.5, Q2AL.6, Q2AL.7, Q2AL.8, Q2AL.9, R203.1, U_D2.18
M2_B: C205.2, P_M2B.1, Q2BH.1, Q2BH.2, Q2BH.3, Q2BL.5, Q2BL.6, Q2BL.7, Q2BL.8, Q2BL.9, R208.1, U_D2.15
M2_BSTA: C203.1, U_D2.20
M2_BSTB: C205.1, U_D2.17
M2_BSTC: C207.1, U_D2.14
M2_C: C207.2, P_M2C.1, Q2CH.1, Q2CH.2, Q2CH.3, Q2CL.5, Q2CL.6, Q2CL.7, Q2CL.8, Q2CL.9, R213.1, U_D2.12
M2_CMP_A: R203.2, R204.1, R205.1, U_E2.27
M2_CMP_B: R208.2, R209.1, R210.1, U_E2.23
M2_CMP_C: R213.2, R214.1, R215.1, U_E2.8
M2_GHA: Q2AH.4, R201.2
M2_GHA_D: R201.1, U_D2.19
M2_GHB: Q2BH.4, R206.2
M2_GHB_D: R206.1, U_D2.16
M2_GHC: Q2CH.4, R211.2
M2_GHC_D: R211.1, U_D2.13
M2_GLA: Q2AL.4, R202.2
M2_GLA_D: R202.1, U_D2.11
M2_GLB: Q2BL.4, R207.2
M2_GLB_D: R207.1, U_D2.10
M2_GLC: Q2CL.4, R212.2
M2_GLC_D: R212.1, U_D2.9
M2_HA: U_D2.22, U_E2.19
M2_HB: U_D2.23, U_E2.18
M2_HC: U_D2.24, U_E2.16
M2_IOUT: R216.1, R218.1, U_A2.6
M2_ISENSE: C210.1, R216.2, R217.1, U_E2.11
M2_LA: U_D2.1, U_E2.15
M2_LB: U_D2.2, U_E2.14
M2_LC: U_D2.3, U_E2.13
M2_NEUTRAL: R205.2, R210.2, R215.2, U_E2.9
M2_SIG: U_E2.24, U_FC.9
M2_SNSN: R_S2.4, U_A2.5
M2_SNSP: R_S2.3, U_A2.4
M2_SRC: C204.2, C206.2, C208.2, Q2AL.1, Q2AL.2, Q2AL.3, Q2BL.1, Q2BL.2, Q2BL.3, Q2CL.1, Q2CL.2, Q2CL.3, R_S2.1
M2_SWCLK: TP_C2.1, U_E2.21
M2_SWDIO: TP_D2.1, U_E2.20
M2_VSENSE: C211.1, R219.2, R220.1, U_E2.12
M3_A: C303.2, P_M3A.1, Q3AH.1, Q3AH.2, Q3AH.3, Q3AL.5, Q3AL.6, Q3AL.7, Q3AL.8, Q3AL.9, R303.1, U_D3.18
M3_B: C305.2, P_M3B.1, Q3BH.1, Q3BH.2, Q3BH.3, Q3BL.5, Q3BL.6, Q3BL.7, Q3BL.8, Q3BL.9, R308.1, U_D3.15
M3_BSTA: C303.1, U_D3.20
M3_BSTB: C305.1, U_D3.17
M3_BSTC: C307.1, U_D3.14
M3_C: C307.2, P_M3C.1, Q3CH.1, Q3CH.2, Q3CH.3, Q3CL.5, Q3CL.6, Q3CL.7, Q3CL.8, Q3CL.9, R313.1, U_D3.12
M3_CMP_A: R303.2, R304.1, R305.1, U_E3.27
M3_CMP_B: R308.2, R309.1, R310.1, U_E3.23
M3_CMP_C: R313.2, R314.1, R315.1, U_E3.8
M3_GHA: Q3AH.4, R301.2
M3_GHA_D: R301.1, U_D3.19
M3_GHB: Q3BH.4, R306.2
M3_GHB_D: R306.1, U_D3.16
M3_GHC: Q3CH.4, R311.2
M3_GHC_D: R311.1, U_D3.13
M3_GLA: Q3AL.4, R302.2
M3_GLA_D: R302.1, U_D3.11
M3_GLB: Q3BL.4, R307.2
M3_GLB_D: R307.1, U_D3.10
M3_GLC: Q3CL.4, R312.2
M3_GLC_D: R312.1, U_D3.9
M3_HA: U_D3.22, U_E3.19
M3_HB: U_D3.23, U_E3.18
M3_HC: U_D3.24, U_E3.16
M3_IOUT: R316.1, R318.1, U_A3.6
M3_ISENSE: C310.1, R316.2, R317.1, U_E3.11
M3_LA: U_D3.1, U_E3.15
M3_LB: U_D3.2, U_E3.14
M3_LC: U_D3.3, U_E3.13
M3_NEUTRAL: R305.2, R310.2, R315.2, U_E3.9
M3_SIG: U_E3.24, U_FC.10
M3_SNSN: R_S3.4, U_A3.5
M3_SNSP: R_S3.3, U_A3.4
M3_SRC: C304.2, C306.2, C308.2, Q3AL.1, Q3AL.2, Q3AL.3, Q3BL.1, Q3BL.2, Q3BL.3, Q3CL.1, Q3CL.2, Q3CL.3, R_S3.1
M3_SWCLK: TP_C3.1, U_E3.21
M3_SWDIO: TP_D3.1, U_E3.20
M3_VSENSE: C311.1, R319.2, R320.1, U_E3.12
M4_A: C403.2, P_M4A.1, Q4AH.1, Q4AH.2, Q4AH.3, Q4AL.5, Q4AL.6, Q4AL.7, Q4AL.8, Q4AL.9, R403.1, U_D4.18
M4_B: C405.2, P_M4B.1, Q4BH.1, Q4BH.2, Q4BH.3, Q4BL.5, Q4BL.6, Q4BL.7, Q4BL.8, Q4BL.9, R408.1, U_D4.15
M4_BSTA: C403.1, U_D4.20
M4_BSTB: C405.1, U_D4.17
M4_BSTC: C407.1, U_D4.14
M4_C: C407.2, P_M4C.1, Q4CH.1, Q4CH.2, Q4CH.3, Q4CL.5, Q4CL.6, Q4CL.7, Q4CL.8, Q4CL.9, R413.1, U_D4.12
M4_CMP_A: R403.2, R404.1, R405.1, U_E4.27
M4_CMP_B: R408.2, R409.1, R410.1, U_E4.23
M4_CMP_C: R413.2, R414.1, R415.1, U_E4.8
M4_GHA: Q4AH.4, R401.2
M4_GHA_D: R401.1, U_D4.19
M4_GHB: Q4BH.4, R406.2
M4_GHB_D: R406.1, U_D4.16
M4_GHC: Q4CH.4, R411.2
M4_GHC_D: R411.1, U_D4.13
M4_GLA: Q4AL.4, R402.2
M4_GLA_D: R402.1, U_D4.11
M4_GLB: Q4BL.4, R407.2
M4_GLB_D: R407.1, U_D4.10
M4_GLC: Q4CL.4, R412.2
M4_GLC_D: R412.1, U_D4.9
M4_HA: U_D4.22, U_E4.19
M4_HB: U_D4.23, U_E4.18
M4_HC: U_D4.24, U_E4.16
M4_IOUT: R416.1, R418.1, U_A4.6
M4_ISENSE: C410.1, R416.2, R417.1, U_E4.11
M4_LA: U_D4.1, U_E4.15
M4_LB: U_D4.2, U_E4.14
M4_LC: U_D4.3, U_E4.13
M4_NEUTRAL: R405.2, R410.2, R415.2, U_E4.9
M4_SIG: U_E4.24, U_FC.11
M4_SNSN: R_S4.4, U_A4.5
M4_SNSP: R_S4.3, U_A4.4
M4_SRC: C404.2, C406.2, C408.2, Q4AL.1, Q4AL.2, Q4AL.3, Q4BL.1, Q4BL.2, Q4BL.3, Q4CL.1, Q4CL.2, Q4CL.3, R_S4.1
M4_SWCLK: TP_C4.1, U_E4.21
M4_SWDIO: TP_D4.1, U_E4.20
M4_VSENSE: C411.1, R419.2, R420.1, U_E4.12
NRST: C22.1, U_FC.7
SPI1_MISO: U_FC.14, U_IMU.1
SPI1_MOSI: U_FC.15, U_IMU.14
SPI1_SCK: U_FC.13, U_IMU.13
UART1_RX: P_R1.1, U_FC.32
UART1_TX: P_T1.1, U_FC.31
UART2_RX: P_R2.1, U_FC.42
UART2_TX: P_T2.1, U_FC.41
USB_CC1: J_USB.A5, R11.1
USB_CC2: J_USB.B5, R12.1
USB_DM: J_USB.A7, J_USB.B7, U_ESD.3, U_ESD.4, U_FC.33
USB_DP: J_USB.A6, J_USB.B6, U_ESD.1, U_ESD.6, U_FC.34
USB_VBUS: D_USB.2, J_USB.A4B9, J_USB.B4A9, U_ESD.5
VBAT: C1.1, C2.1, C104.1, C106.1, C108.1, C204.1, C206.1, C208.1, C304.1, C306.1, C308.1, C404.1, C406.1, C408.1, D_TVS.1, P_BAT+.1, Q1AH.5, Q1AH.6, Q1AH.7, Q1AH.8, Q1AH.9, Q1BH.5, Q1BH.6, Q1BH.7, Q1BH.8, Q1BH.9, Q1CH.5, Q1CH.6, Q1CH.7, Q1CH.8, Q1CH.9, Q2AH.5, Q2AH.6, Q2AH.7, Q2AH.8, Q2AH.9, Q2BH.5, Q2BH.6, Q2BH.7, Q2BH.8, Q2BH.9, Q2CH.5, Q2CH.6, Q2CH.7, Q2CH.8, Q2CH.9, Q3AH.5, Q3AH.6, Q3AH.7, Q3AH.8, Q3AH.9, Q3BH.5, Q3BH.6, Q3BH.7, Q3BH.8, Q3BH.9, Q3CH.5, Q3CH.6, Q3CH.7, Q3CH.8, Q3CH.9, Q4AH.5, Q4AH.6, Q4AH.7, Q4AH.8, Q4AH.9, Q4BH.5, Q4BH.6, Q4BH.7, Q4BH.8, Q4BH.9, Q4CH.5, Q4CH.6, Q4CH.7, Q4CH.8, Q4CH.9, R1.1, R3.1, R6.1, R119.1, R219.1, R319.1, R419.1, U_BEC.4
